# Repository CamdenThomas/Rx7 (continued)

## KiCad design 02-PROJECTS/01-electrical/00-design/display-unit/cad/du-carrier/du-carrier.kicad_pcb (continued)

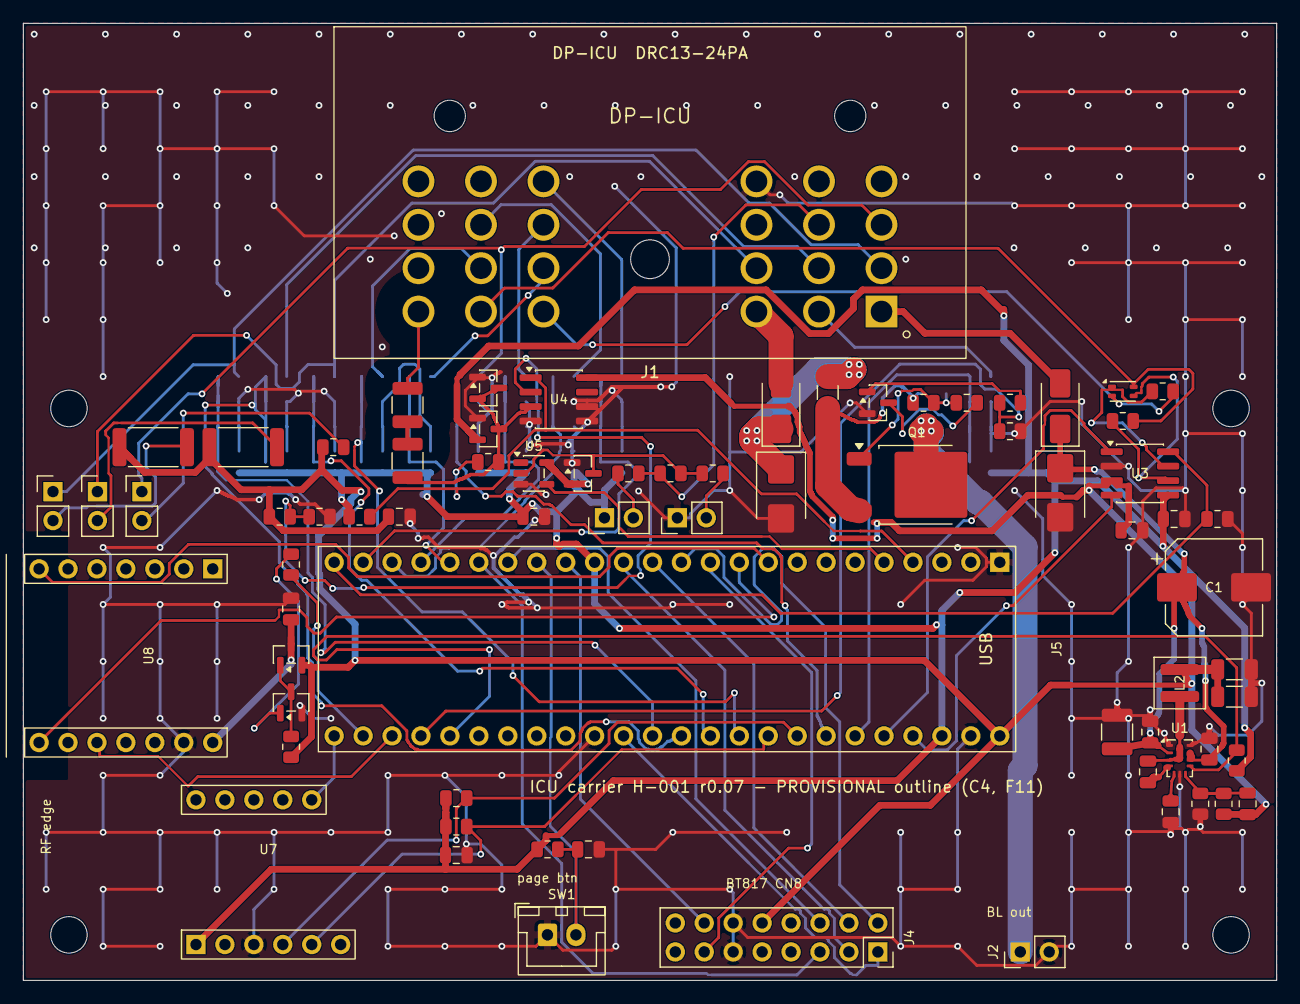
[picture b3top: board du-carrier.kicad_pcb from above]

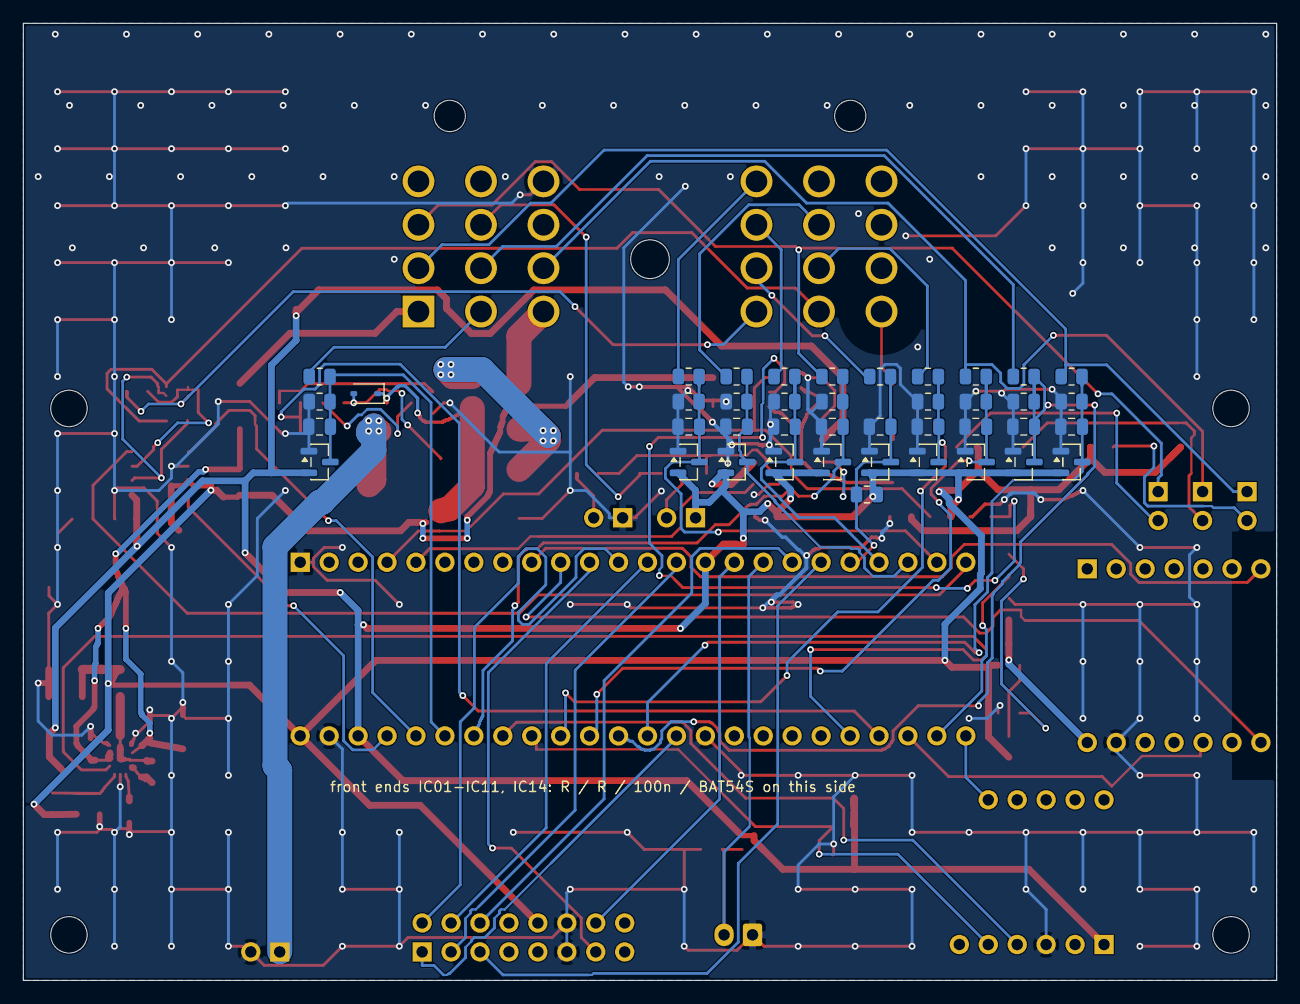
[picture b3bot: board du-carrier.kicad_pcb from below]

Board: 2 copper layers, 110.0 x 84.0 mm, 118 parts (41 on the bottom side), 77 nets.

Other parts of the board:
H1, H2, H3, H4: M3 - confirm at C4/F11; MountingHole_3.2mm_M3

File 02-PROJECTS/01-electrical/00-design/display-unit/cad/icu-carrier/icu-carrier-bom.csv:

"Refs","Value","Footprint","Qty","DNP"
"C1","68u 63V","Capacitor_SMD:CP_Elec_8x10","1",""
"C2","22u 16V","Capacitor_SMD:C_1206_3216Metric","1",""
"C3","100n","Capacitor_SMD:C_0805_2012Metric","1",""
"C4","100n","Capacitor_SMD:C_0805_2012Metric","1",""
"C5","100n","Capacitor_SMD:C_0805_2012Metric","1",""
"C6","100n","Capacitor_SMD:C_0805_2012Metric","1",""
"C7","100n","Capacitor_SMD:C_0805_2012Metric","1",""
"C8","100n","Capacitor_SMD:C_0805_2012Metric","1",""
"C9","100n","Capacitor_SMD:C_0805_2012Metric","1",""
"C10","100n","Capacitor_SMD:C_0805_2012Metric","1",""
"C11","100n","Capacitor_SMD:C_0805_2012Metric","1",""
"C12","100n","Capacitor_SMD:C_0805_2012Metric","1",""
"C13","100n","Capacitor_SMD:C_0805_2012Metric","1",""
"C14","100n","Capacitor_SMD:C_0805_2012Metric","1",""
"C15","100n","Capacitor_SMD:C_0805_2012Metric","1",""
"C16","100n","Capacitor_SMD:C_0805_2012Metric","1",""
"C17","100n","Capacitor_SMD:C_0805_2012Metric","1",""
"C18","100n","Capacitor_SMD:C_0805_2012Metric","1",""
"C19","10u","Capacitor_SMD:C_0805_2012Metric","1",""
"C20","4.7u 100V X7R","Capacitor_SMD:C_1210_3225Metric","1",""
"C21","220n 100V","Capacitor_SMD:C_0805_2012Metric","1",""
"C22","220n 100V","Capacitor_SMD:C_0805_2012Metric","1",""
"C23","22u 10V X7R","Capacitor_SMD:C_1206_3216Metric","1",""
"C24","100n 16V","Capacitor_SMD:C_0805_2012Metric","1",""
"C25","1u 16V","Capacitor_SMD:C_0805_2012Metric","1",""
"C26","20p C0G","Capacitor_SMD:C_0805_2012Metric","1",""
"D1","BAT54S","Package_TO_SOT_SMD:SOT-23","1",""
"D2","BAT54S","Package_TO_SOT_SMD:SOT-23","1",""
"D3","BAT54S","Package_TO_SOT_SMD:SOT-23","1",""
"D4","BAT54S","Package_TO_SOT_SMD:SOT-23","1",""
"D5","BAT54S","Package_TO_SOT_SMD:SOT-23","1",""
"D6","BAT54S","Package_TO_SOT_SMD:SOT-23","1",""
"D7","BAT54S","Package_TO_SOT_SMD:SOT-23","1",""
"D8","BAT54S","Package_TO_SOT_SMD:SOT-23","1",""
"D9","BAT54S","Package_TO_SOT_SMD:SOT-23","1",""
"D10","BAT54S","Package_TO_SOT_SMD:SOT-23","1",""
"D20","BZX84C5V1","Package_TO_SOT_SMD:SOT-23","1",""
"D21","BAT54S","Package_TO_SOT_SMD:SOT-23","1",""
"D22","BAT54S","Package_TO_SOT_SMD:SOT-23","1",""
"D23","SL310A","Diode_SMD:D_SMA","1",""
"D24","SMBJ33A","Diode_SMD:D_SMB","1",""
"D25","SL310A","Diode_SMD:D_SMA","1",""
"D26","SMBJ33A","Diode_SMD:D_SMB","1",""
"D27","MM3Z15VT1G","Diode_SMD:D_SOD-323","1",""
"F1","4 A","Fuse:Fuse_1206_3216Metric","1",""
"J1","DRC13-24PA","icu-carrier:DRC13-24PA","1",""
"J2","backlight out","Connector_PinHeader_2.54mm:PinHeader_1x02_P2.54mm_Vertical","1",""
"J4","ME817EV CN8 - 2x8 host header, JP1 2-3 (5 V from this board)","Connector_PinSocket_2.54mm:PinSocket_2x08_P2.54mm_Vertical","1",""
"J5","Teensy 4.1 socket - 2 x 24 female headers (D-259)","icu-carrier:Teensy41_Socket","1",""
"JP1","J1  FITTED","Connector_PinHeader_2.54mm:PinHeader_1x02_P2.54mm_Vertical","1",""
"JP2","J3  FITTED","Connector_PinHeader_2.54mm:PinHeader_1x02_P2.54mm_Vertical","1",""
"JP3","J7  NOT FITTED","Connector_PinHeader_2.54mm:PinHeader_1x02_P2.54mm_Vertical","1",""
"JP8A1","J8A  open collector","Connector_PinHeader_2.54mm:PinHeader_1x02_P2.54mm_Vertical","1",""
"JP8B1","J8B  push-pull","Connector_PinHeader_2.54mm:PinHeader_1x02_P2.54mm_Vertical","1",""
"L1","common-mode choke - DNP; fit only with R44 / R45 removed","Inductor_SMD:L_CommonModeChoke_Coilank_ACM2012","1","DNP"
"L2","2.2u XAL4020-222","Inductor_SMD:L_Coilcraft_XAL4020-XXX","1",""
"Q1","SQD50P06 class, >= 60 V","Package_TO_SOT_SMD:TO-252-2","1",""
"Q2","MMBT5551","Package_TO_SOT_SMD:SOT-23","1",""
"Q3","DMG3415U class P-FET, SOT-23 - confirm","Package_TO_SOT_SMD:SOT-23","1",""
"Q4","MMBT3904","Package_TO_SOT_SMD:SOT-23","1",""
"R1","10k","Resistor_SMD:R_0805_2012Metric","1",""
"R2","4.7k","Resistor_SMD:R_0805_2012Metric","1",""
"R3","10k","Resistor_SMD:R_0805_2012Metric","1",""
"R4","100k","Resistor_SMD:R_0805_2012Metric","1",""
"R5","10k","Resistor_SMD:R_0805_2012Metric","1",""
"R6","100R 1W","Resistor_SMD:R_2512_6332Metric","1",""
"R7","15k","Resistor_SMD:R_0805_2012Metric","1",""
"R8","10k","Resistor_SMD:R_0805_2012Metric","1",""
"R9","15k","Resistor_SMD:R_0805_2012Metric","1",""
"R10","10k","Resistor_SMD:R_0805_2012Metric","1",""
"R11","100R 1W","Resistor_SMD:R_2512_6332Metric","1",""
"R12","15k","Resistor_SMD:R_0805_2012Metric","1",""
"R13","10k","Resistor_SMD:R_0805_2012Metric","1",""
"R14","47k","Resistor_SMD:R_0805_2012Metric","1",""
"R15","10k","Resistor_SMD:R_0805_2012Metric","1",""
"R16","1k","Resistor_SMD:R_0805_2012Metric","1",""
"R17","10k","Resistor_SMD:R_0805_2012Metric","1",""
"R18","1k - 2.2k 1%  ?","Resistor_SMD:R_0805_2012Metric","1",""
"R19","15k","Resistor_SMD:R_0805_2012Metric","1",""
"R20","10k","Resistor_SMD:R_0805_2012Metric","1",""
"R21","22k","Resistor_SMD:R_0805_2012Metric","1",""
"R22","10k","Resistor_SMD:R_0805_2012Metric","1",""
"R23","22k","Resistor_SMD:R_0805_2012Metric","1",""
"R24","10k","Resistor_SMD:R_0805_2012Metric","1",""
"R25","22k","Resistor_SMD:R_0805_2012Metric","1",""
"R26","10k","Resistor_SMD:R_0805_2012Metric","1",""
"R27","47k","Resistor_SMD:R_0805_2012Metric","1",""
"R28","10k","Resistor_SMD:R_0805_2012Metric","1",""
"R29","100k 0.5W","Resistor_SMD:R_1210_3225Metric","1",""
"R30","100k 0.5W","Resistor_SMD:R_1210_3225Metric","1",""
"R31","39k","Resistor_SMD:R_0805_2012Metric","1",""
"R32","12k","Resistor_SMD:R_0805_2012Metric","1",""
"R33","1.2M","Resistor_SMD:R_0805_2012Metric","1",""
"R34","10k","Resistor_SMD:R_0805_2012Metric","1",""
"R35","4.7k","Resistor_SMD:R_0805_2012Metric","1",""
"R36","10k","Resistor_SMD:R_0805_2012Metric","1",""
"R37","4.7k","Resistor_SMD:R_0805_2012Metric","1",""
"R38","10k","Resistor_SMD:R_0805_2012Metric","1",""
"R39","4.7k","Resistor_SMD:R_0805_2012Metric","1",""
"R40","4.7k","Resistor_SMD:R_0805_2012Metric","1",""
"R41","100k 1%","Resistor_SMD:R_0805_2012Metric","1",""
"R42","24.9k 1%","Resistor_SMD:R_0805_2012Metric","1",""
"R43","100k","Resistor_SMD:R_0805_2012Metric","1",""
"R44","0R","Resistor_SMD:R_0805_2012Metric","1",""
"R45","0R","Resistor_SMD:R_0805_2012Metric","1",""
"R46","10k","Resistor_SMD:R_0805_2012Metric","1",""
"R47","10k","Resistor_SMD:R_0805_2012Metric","1",""
"SW1","IC22","Connector_JST:JST_XH_B2B-XH-A_1x02_P2.50mm_Vertical","1",""
"U1","LMR36015FSCQ-Q1","Package_DFN_QFN:Texas_RNX0012C_VQFN-14-11-1EP_2x3mm_P0.5mm_EP0.25x1.825mm","1",""
"U2","VN5E class, >= 6 A - DNP","","1","DNP"
"U3","TCAN1042HVDRQ1","Package_SO:SOIC-8_3.9x4.9mm_P1.27mm","1",""
"U4","LM393","Package_SO:SOIC-8_3.9x4.9mm_P1.27mm","1",""
"U5","74LVC1G17","Package_TO_SOT_SMD:SOT-23-5","1",""
"U7","Adafruit 4517 LSM6DSOX+LIS3MDL (LSM6DSO class, P109 - confirm the board bought)","icu-carrier:IMU_Adafruit_4517_Socket","1",""
"U8","XIAO ESP32C3 2x7 socket (Seeed, S-490)","icu-carrier:XIAO_ESP32C3_Socket_2x07","1",""

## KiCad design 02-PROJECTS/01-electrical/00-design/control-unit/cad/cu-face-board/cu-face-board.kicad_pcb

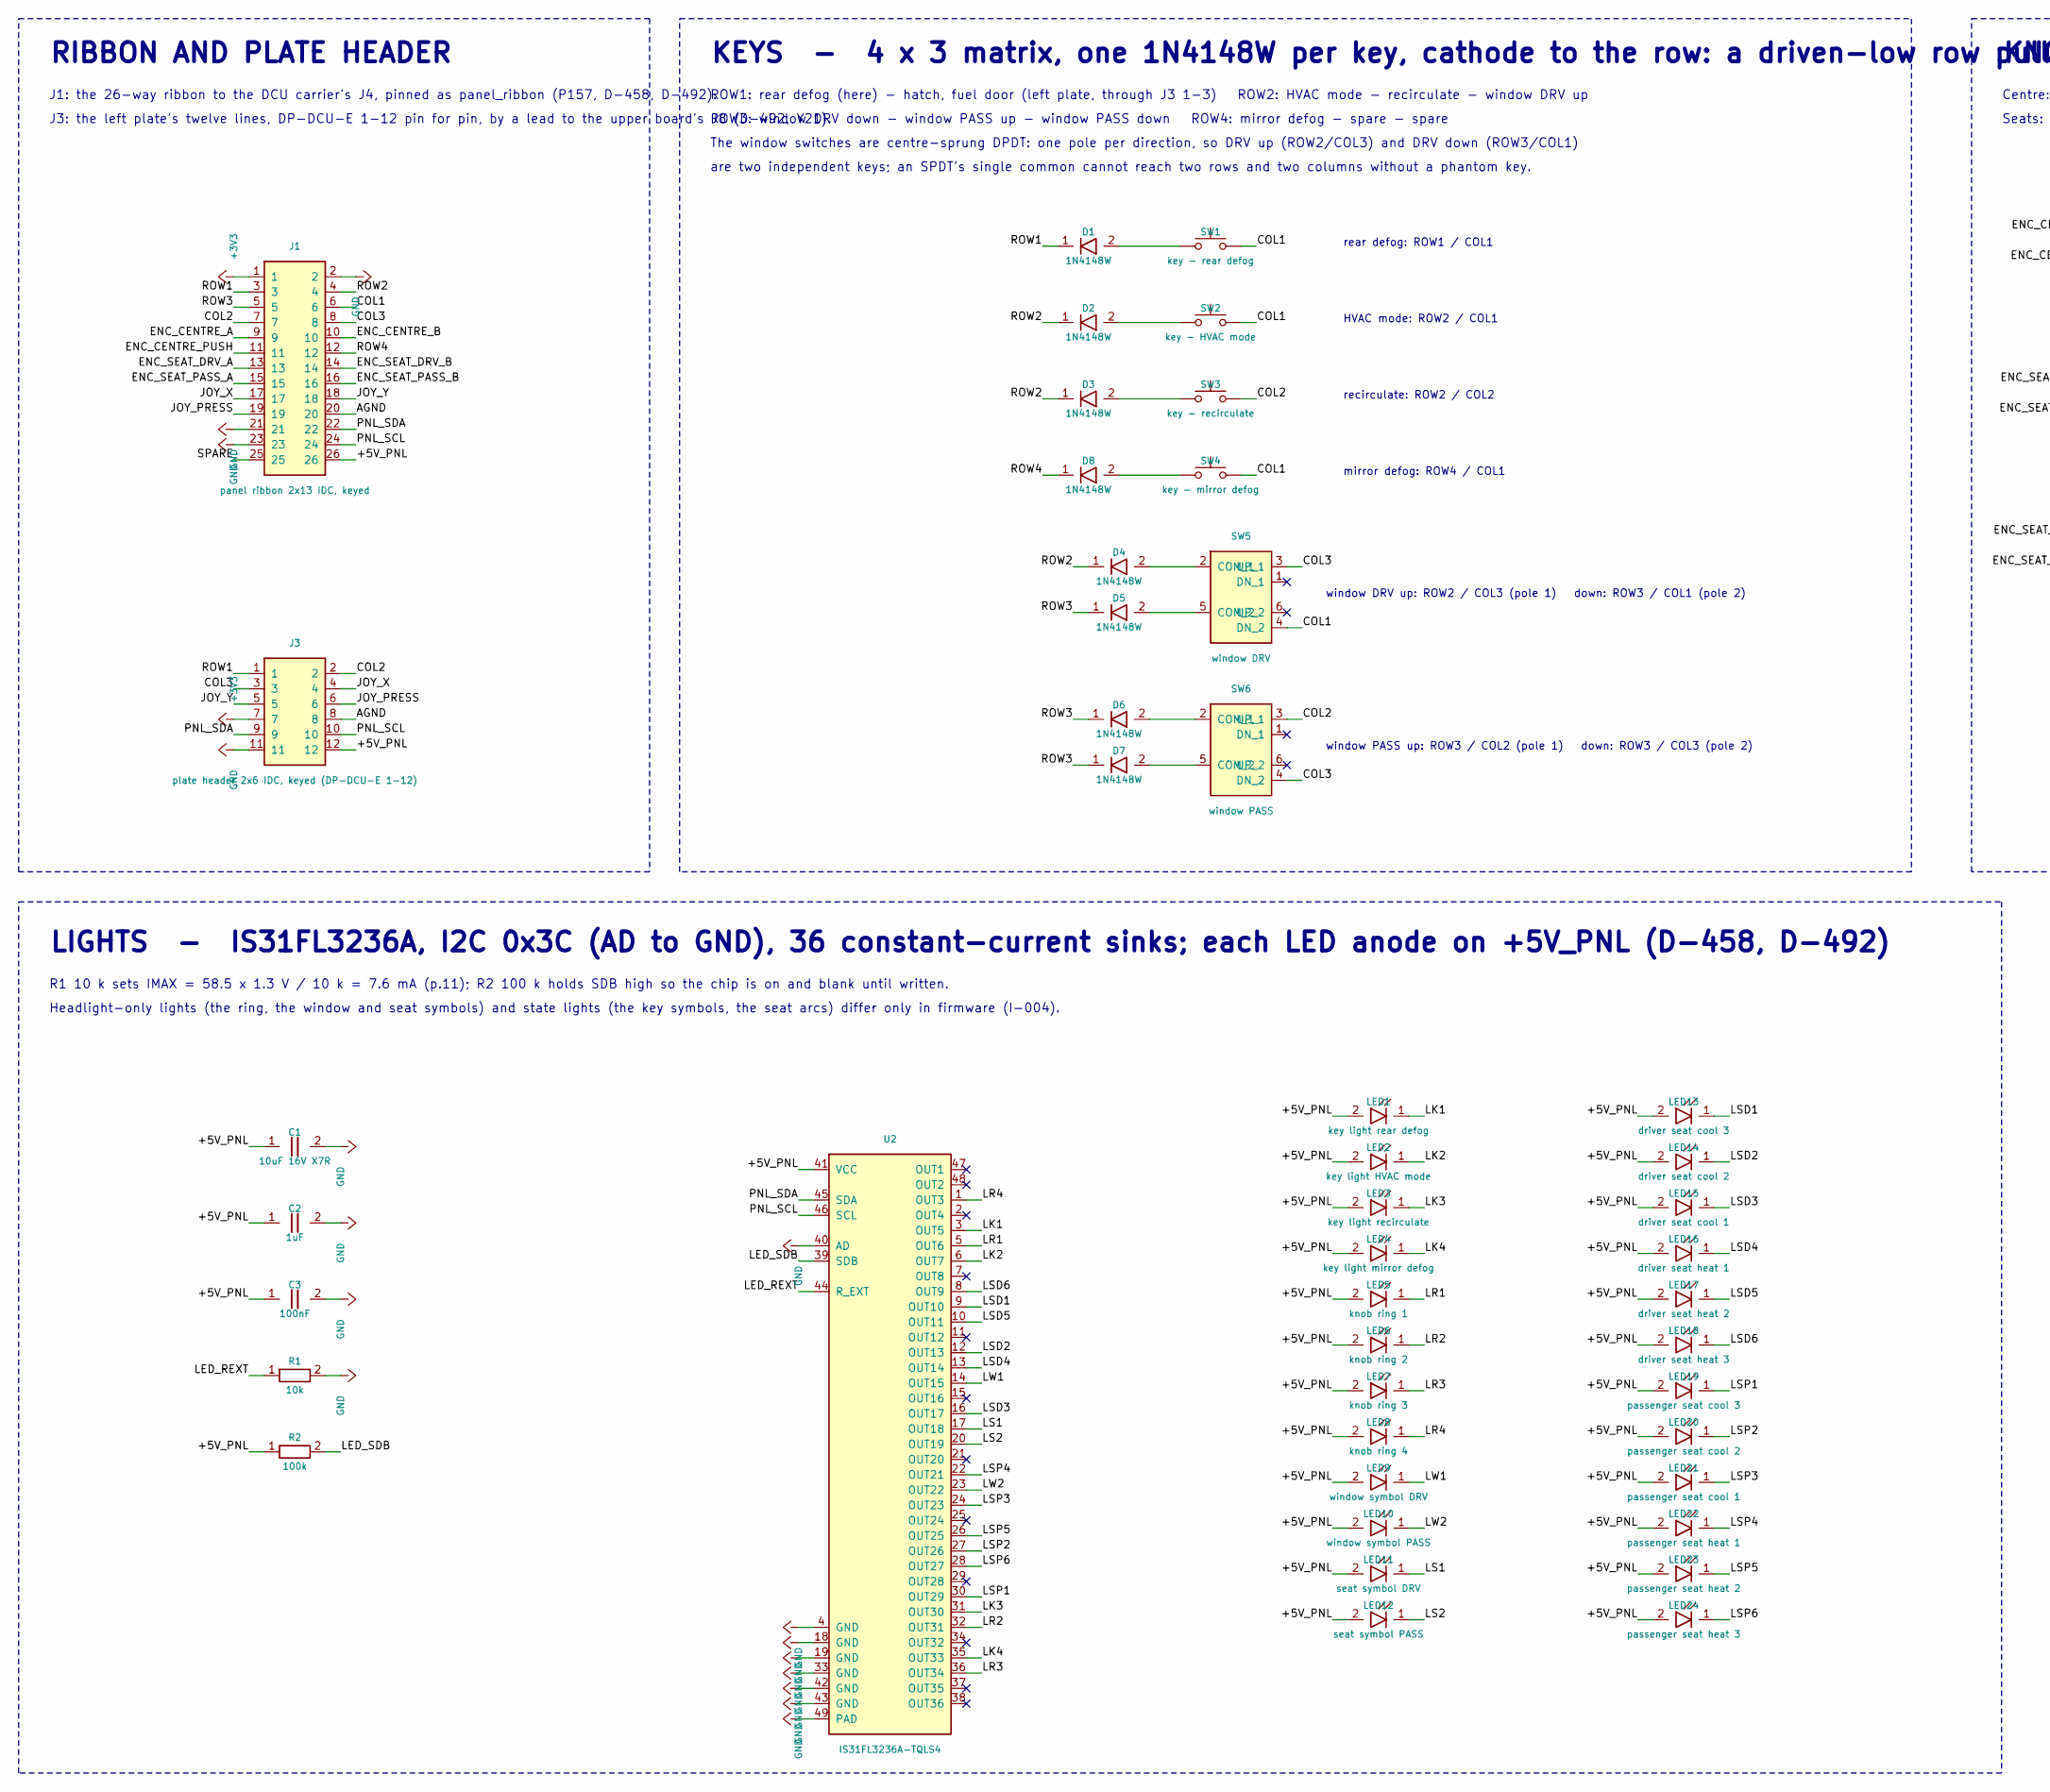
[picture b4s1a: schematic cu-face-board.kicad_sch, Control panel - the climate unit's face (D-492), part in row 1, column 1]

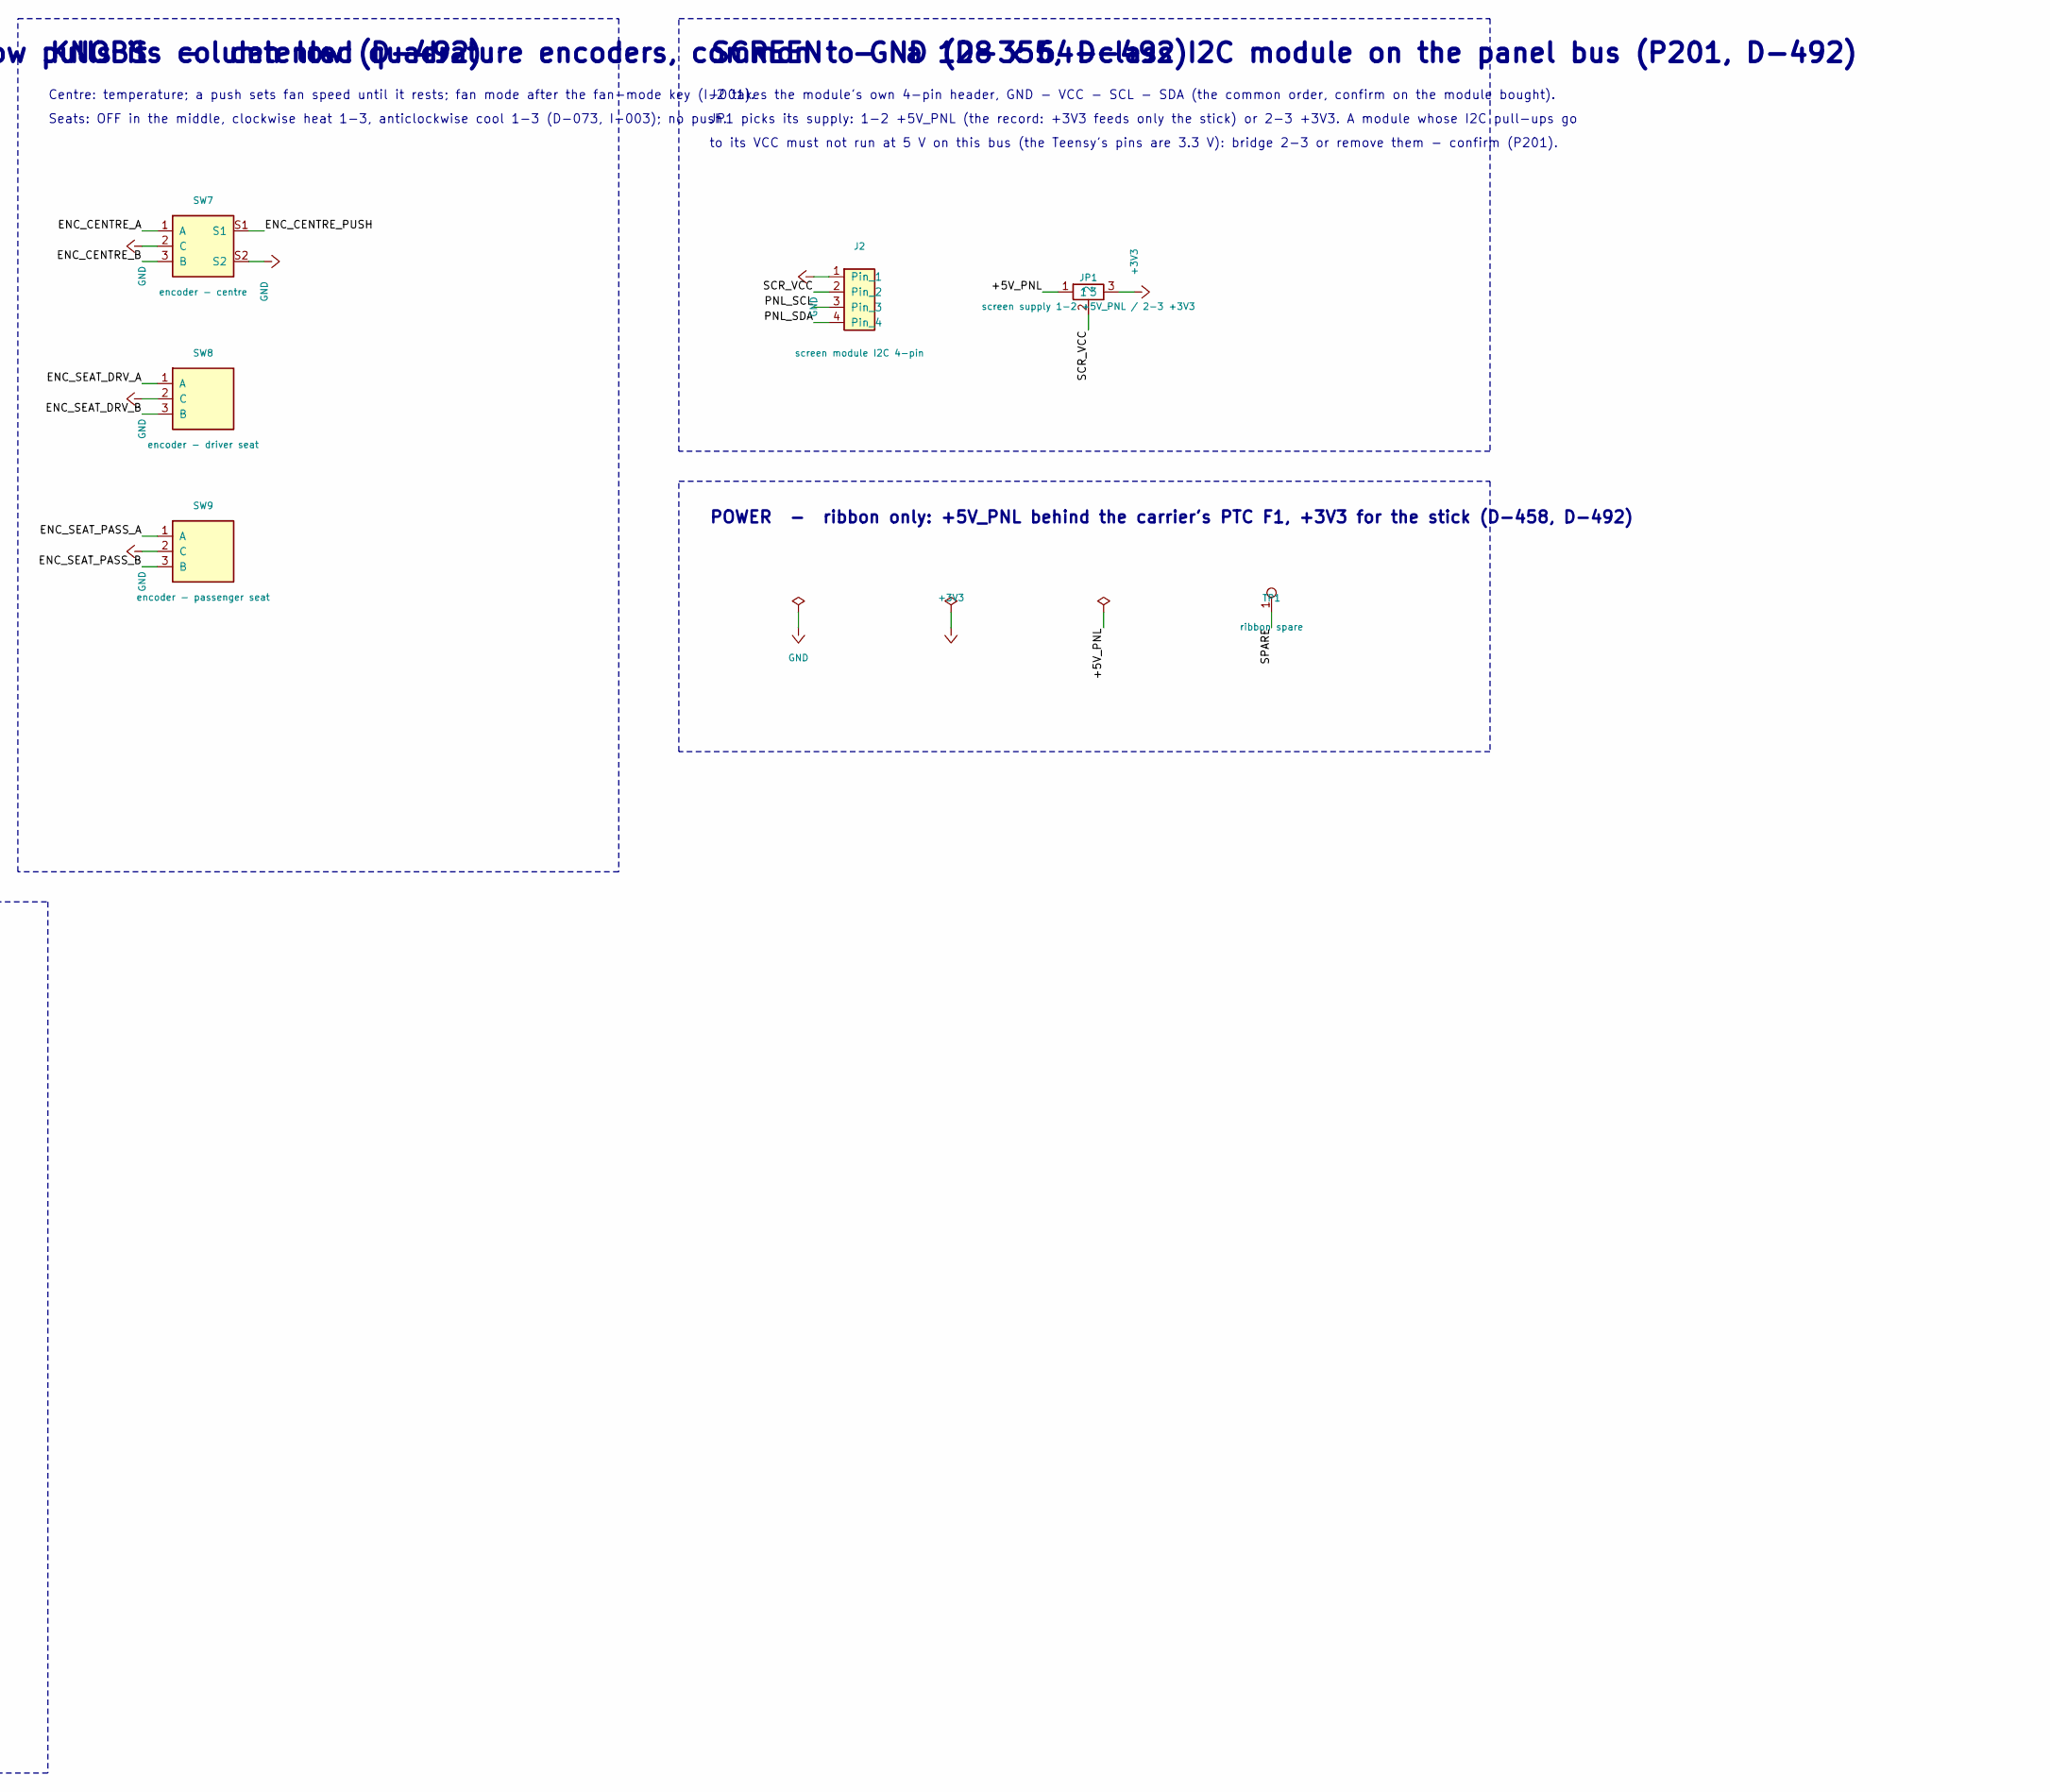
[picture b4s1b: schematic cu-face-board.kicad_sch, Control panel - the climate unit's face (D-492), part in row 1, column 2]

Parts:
C1: 10uF 16V X7R; C_0805_2012Metric
C2: 1uF; C_0603_1608Metric
C3: 100nF; C_0603_1608Metric
D1, D2, D3, D4, D5, D6, D7, D8: 1N4148W; D_SOD-123
J1: panel ribbon 2x13 IDC, keyed; IDC-Header_2x13_P2.54mm_Vertical
J2: screen module I2C 4-pin; PinHeader_1x04_P2.54mm_Vertical
J3: plate header 2x6 IDC, keyed (DP-DCU-E 1-12); IDC-Header_2x06_P2.54mm_Vertical
JP1: screen supply 1-2 +5V_PNL / 2-3 +3V3; SolderJumper-3_P1.3mm_Open_RoundedPad1.0x1.5mm
LED1: key light rear defog; LED_0603_1608Metric
LED2: key light HVAC mode; LED_0603_1608Metric
LED3: key light recirculate; LED_0603_1608Metric
LED4: key light mirror defog; LED_0603_1608Metric
LED5: knob ring 1; LED_0603_1608Metric
LED6: knob ring 2; LED_0603_1608Metric
LED7: knob ring 3; LED_0603_1608Metric
LED8: knob ring 4; LED_0603_1608Metric
LED9: window symbol DRV; LED_0603_1608Metric
LED10: window symbol PASS; LED_0603_1608Metric
LED11: seat symbol DRV; LED_0603_1608Metric
LED12: seat symbol PASS; LED_0603_1608Metric
LED13: driver seat cool 3; LED_0603_1608Metric
LED14: driver seat cool 2; LED_0603_1608Metric
LED15: driver seat cool 1; LED_0603_1608Metric
LED16: driver seat heat 1; LED_0603_1608Metric
LED17: driver seat heat 2; LED_0603_1608Metric
LED18: driver seat heat 3; LED_0603_1608Metric
LED19: passenger seat cool 3; LED_0603_1608Metric
LED20: passenger seat cool 2; LED_0603_1608Metric
LED21: passenger seat cool 1; LED_0603_1608Metric
LED22: passenger seat heat 1; LED_0603_1608Metric
LED23: passenger seat heat 2; LED_0603_1608Metric
LED24: passenger seat heat 3; LED_0603_1608Metric
R1: 10k; R_0603_1608Metric
R2: 100k; R_0603_1608Metric
SW1: key - rear defog; SW_PUSH_6mm_H13mm
SW2: key - HVAC mode; SW_PUSH_6mm_H13mm
SW3: key - recirculate; SW_PUSH_6mm_H13mm
SW4: key - mirror defog; SW_PUSH_6mm_H13mm
SW5: window DRV; Toggle_DPDT_SubMini_2x3_P2.54mm
SW6: window PASS; Toggle_DPDT_SubMini_2x3_P2.54mm
SW7: encoder - centre; RotaryEncoder_Bourns_Vertical_PEC11R-4xxxF-Sxxxx
SW8: encoder - driver seat; RotaryEncoder_Bourns_Vertical_PEC11R-4xxxF-Sxxxx
SW9: encoder - passenger seat; RotaryEncoder_Bourns_Vertical_PEC11R-4xxxF-Sxxxx
TP1: ribbon spare; TestPoint_Pad_D1.5mm
U2: IS31FL3236A-TQLS4; TQFP-48-1EP_7x7mm_P0.5mm_EP4.11x4.11mm

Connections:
+3V3: J1.1, J3.7, JP1.3
/+5V_PNL: C1.1, C2.1, C3.1, J1.26, J3.12, JP1.1, LED1.2 (A), LED2.2 (A), LED3.2 (A), LED4.2 (A), LED5.2 (A), LED6.2 (A), LED7.2 (A), LED8.2 (A), LED9.2 (A), LED10.2 (A), LED11.2 (A), LED12.2 (A), LED13.2 (A), LED14.2 (A), LED15.2 (A), LED16.2 (A), LED17.2 (A), LED18.2 (A), LED19.2 (A), LED20.2 (A), LED21.2 (A), LED22.2 (A), LED23.2 (A), LED24.2 (A), R2.1, U2.41 (VCC)
/AGND: J1.20, J3.8
/COL1: J1.6, SW1.2, SW2.2, SW4.2, SW5.4 (DN_2)
/COL2: J1.7, J3.2, SW3.2, SW6.3 (UP_1)
/COL3: J1.8, J3.3, SW5.3 (UP_1), SW6.4 (DN_2)
/ENC_CENTRE_A: J1.9, SW7.1 (A)
/ENC_CENTRE_B: J1.10, SW7.3 (B)
/ENC_CENTRE_PUSH: J1.11, SW7.S1
/ENC_SEAT_DRV_A: J1.13, SW8.1 (A)
/ENC_SEAT_DRV_B: J1.14, SW8.3 (B)
/ENC_SEAT_PASS_A: J1.15, SW9.1 (A)
/ENC_SEAT_PASS_B: J1.16, SW9.3 (B)
/JOY_PRESS: J1.19, J3.6
/JOY_X: J1.17, J3.4
/JOY_Y: J1.18, J3.5
/LED_REXT: R1.1, U2.44 (R_EXT)
/LED_SDB: R2.2, U2.39 (SDB)
/LK1: LED1.1 (K), U2.3 (OUT5)
/LK2: LED2.1 (K), U2.6 (OUT7)
/LK3: LED3.1 (K), U2.31 (OUT30)
/LK4: LED4.1 (K), U2.35 (OUT33)
/LR1: LED5.1 (K), U2.5 (OUT6)
/LR2: LED6.1 (K), U2.32 (OUT31)
/LR3: LED7.1 (K), U2.36 (OUT34)
/LR4: LED8.1 (K), U2.1 (OUT3)
/LS1: LED11.1 (K), U2.17 (OUT18)
/LS2: LED12.1 (K), U2.20 (OUT19)
/LSD1: LED13.1 (K), U2.9 (OUT10)
/LSD2: LED14.1 (K), U2.12 (OUT13)
/LSD3: LED15.1 (K), U2.16 (OUT17)
/LSD4: LED16.1 (K), U2.13 (OUT14)
/LSD5: LED17.1 (K), U2.10 (OUT11)
/LSD6: LED18.1 (K), U2.8 (OUT9)
/LSP1: LED19.1 (K), U2.30 (OUT29)
/LSP2: LED20.1 (K), U2.27 (OUT26)
/LSP3: LED21.1 (K), U2.24 (OUT23)
/LSP4: LED22.1 (K), U2.22 (OUT21)
/LSP5: LED23.1 (K), U2.26 (OUT25)
/LSP6: LED24.1 (K), U2.28 (OUT27)
/LW1: LED9.1 (K), U2.14 (OUT15)
/LW2: LED10.1 (K), U2.23 (OUT22)
/PNL_SCL: J1.24, J2.3, J3.10, U2.46 (SCL)
/PNL_SDA: J1.22, J2.4, J3.9, U2.45 (SDA)
/ROW1: D1.1 (K), J1.3, J3.1
/ROW2: D2.1 (K), D3.1 (K), D4.1 (K), J1.4
/ROW3: D5.1 (K), D6.1 (K), D7.1 (K), J1.5
/ROW4: D8.1 (K), J1.12
/SCR_VCC: J2.2, JP1.2
/SPARE: J1.25, TP1.1
GND: C1.2, C2.2, C3.2, J1.2, J1.21, J1.23, J2.1, J3.11, R1.2, SW7.2 (C), SW7.S2, SW8.2 (C), SW9.2 (C), U2.4 (GND), U2.18 (GND), U2.19 (GND), U2.33 (GND), U2.40 (AD), U2.42 (GND), U2.43 (GND), U2.49 (PAD)
unnamed: D1.2 (A), SW1.1
unnamed: D2.2 (A), SW2.1
unnamed: D3.2 (A), SW3.1
unnamed: D4.2 (A), SW5.2 (COM_1)
unnamed: D5.2 (A), SW5.5 (COM_2)
unnamed: D6.2 (A), SW6.2 (COM_1)
unnamed: D7.2 (A), SW6.5 (COM_2)
unnamed: D8.2 (A), SW4.1

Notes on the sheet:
RIBBON AND PLATE HEADER
J1: the 26-way ribbon to the DCU carrier's J4, pinned as panel_ribbon (P157, D-458, D-492).
J3: the left plate's twelve lines, DP-DCU-E 1-12 pin for pin, by a lead to the upper board's J8 (D-492, Y21).
KEYS - 4 x 3 matrix, one 1N4148W per key, cathode to the row: a driven-low row pulls its column low (D-492)
ROW1: rear defog (here) - hatch, fuel door (left plate, through J3 1-3) ROW2: HVAC mode - recirculate - window DRV up
ROW3: window DRV down - window PASS up - window PASS down ROW4: mirror defog - spare - spare
The window switches are centre-sprung DPDT: one pole per direction, so DRV up (ROW2/COL3) and DRV down (ROW3/COL1)
are two independent keys; an SPDT's single common cannot reach two rows and two columns without a phantom key.
rear defog: ROW1 / COL1
HVAC mode: ROW2 / COL1
recirculate: ROW2 / COL2
mirror defog: ROW4 / COL1
window DRV up: ROW2 / COL3 (pole 1) down: ROW3 / COL1 (pole 2)
window PASS up: ROW3 / COL2 (pole 1) down: ROW3 / COL3 (pole 2)
KNOBS - detented quadrature encoders, common to GND (D-355, D-492)
Centre: temperature; a push sets fan speed until it rests; fan mode after the fan-mode key (I-001).
Seats: OFF in the middle, clockwise heat 1-3, anticlockwise cool 1-3 (D-073, I-003); no push.
SCREEN - a 128 x 64-class I2C module on the panel bus (P201, D-492)
J2 takes the module's own 4-pin header, GND - VCC - SCL - SDA (the common order, confirm on the module bought).
JP1 picks its supply: 1-2 +5V_PNL (the record: +3V3 feeds only the stick) or 2-3 +3V3. A module whose I2C pull-ups go
to its VCC must not run at 5 V on this bus (the Teensy's pins are 3.3 V): bridge 2-3 or remove them - confirm (P201).
POWER - ribbon only: +5V_PNL behind the carrier's PTC F1, +3V3 for the stick (D-458, D-492)
LIGHTS - IS31FL3236A, I2C 0x3C (AD to GND), 36 constant-current sinks; each LED anode on +5V_PNL (D-458, D-492)
R1 10 k sets IMAX = 58.5 x 1.3 V / 10 k = 7.6 mA (p.11); R2 100 k holds SDB high so the chip is on and blank until written.
Headlight-only lights (the ring, the window and seat symbols) and state lights (the key symbols, the seat arcs) differ only in firmware (I-004).
